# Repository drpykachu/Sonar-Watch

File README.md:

# Sonar Watch

### Hello all! 

### This project is inspired by something that I wanted to buy, but could not find online - so I decided to make it.

<div align="center">
  
</div>

### When the button is pressed, the watch sends out a "ping" to find the location of the hour (inner radial dot) and minute (outer radial dot), thus telling the time.

<div align="center">
  
  <br/>
  
  <br/>
  
  <br/>
  
</div>

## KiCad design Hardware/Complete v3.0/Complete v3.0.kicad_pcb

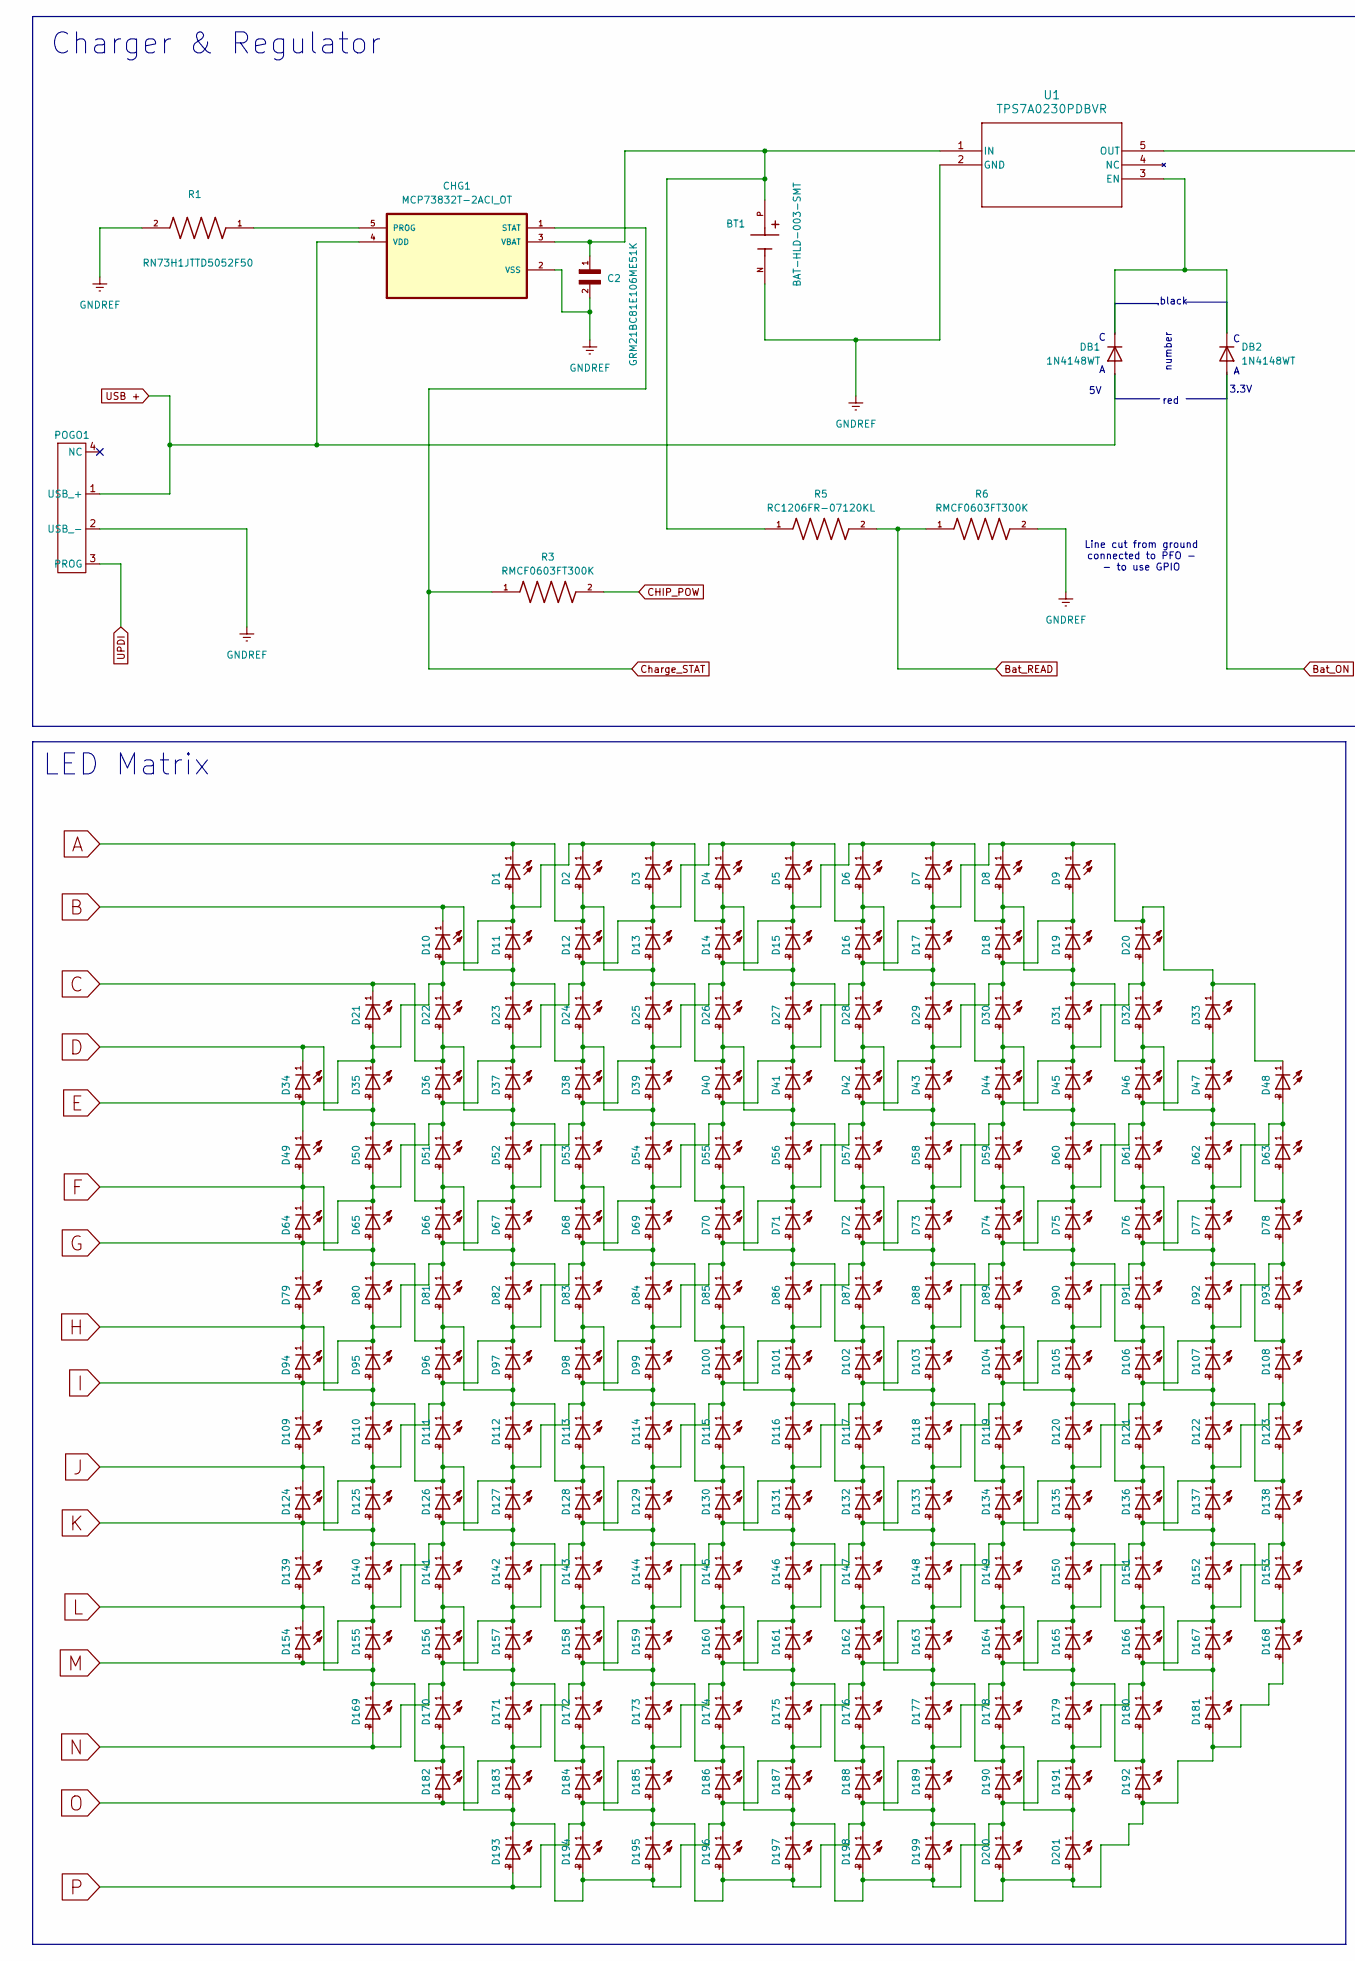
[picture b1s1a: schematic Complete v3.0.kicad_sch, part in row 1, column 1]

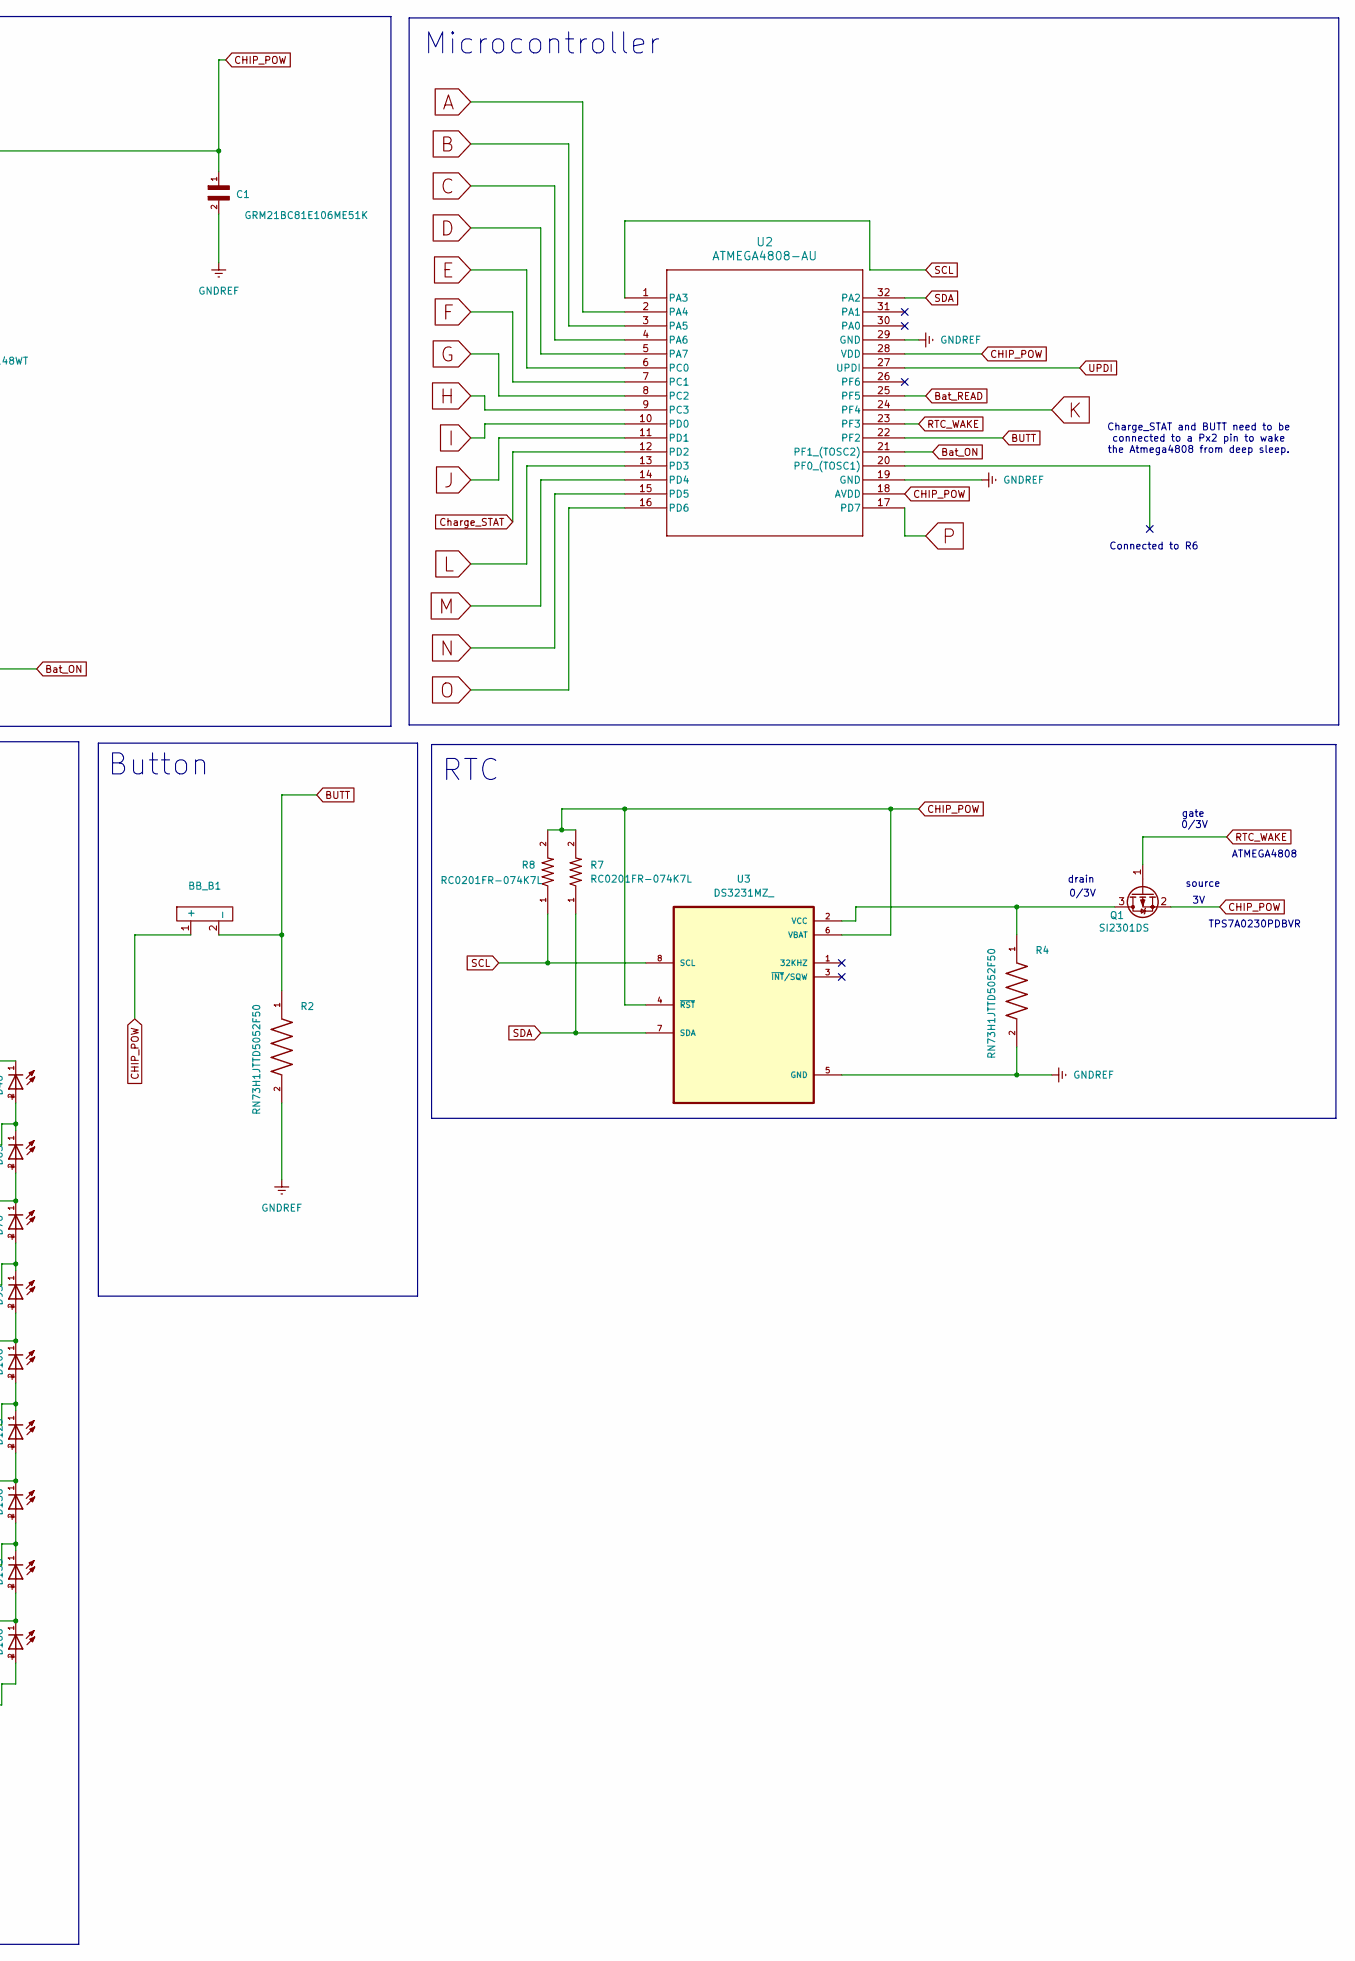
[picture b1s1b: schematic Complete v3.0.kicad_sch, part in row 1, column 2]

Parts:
BB_B1: BB_B
BT1: BAT-HLD-003-SMT; BAT_BAT-HLD-003-SMT_CUT; DigiKey_Part_Number 343-BAT-HLD-003-SMT-ND
C1, C2: GRM21BC81E106ME51K; CAPC2012X140N
CHG1: MCP73832T-2ACI_OT; SOT95P270X145-5N
D1, D2, D3, D4, D5, D6, D7, D8, D9, D10, D11, D12, D13, D14, D15, D16, D17, D18, D19, D20, D21, D22, D23, D24, D25, D26, D27, D28, D29, D30, D31, D32, D33, D34, D35, D36, D37, D38, D39, D40, D41, D42, D43, D44, D45, D46, D47, D48, D49, D50, D51, D52, D53, D54, D55, D56, D57, D58, D59, D60, D61, D62, D63, D64, D65, D66, D67, D68, D69, D70, D71, D72, D73, D74, D75, D76, D77, D78, D79, D80, D81, D82, D83, D84, D85, D86, D87, D88, D89, D90, D91, D92, D93, D94, D95, D96, D97, D98, D99, D100, D101, D102, D103, D104, D105, D106, D107, D108, D109, D110, D111, D112, D113, D114, D115, D116, D117, D118, D119, D120, D121, D122, D123, D124, D125, D126, D127, D128, D129, D130, D131, D132, D133, D134, D135, D136, D137, D138, D139, D140, D141, D142, D143, D144, D145, D146, D147, D148, D149, D150, D151, D152, D153, D154, D155, D156, D157, D158, D159, D160, D161, D162, D163, D164, D165, D166, D167, D168, D169, D170, D171, D172, D173, D174, D175, D176, D177, D178, D179, D180, D181, D182, D183, D184, D185, D186, D187, D188, D189, D190, D191, D192, D193, D194, D195, D196, D197, D198, D199, D200, D201: WL-SMCC_0402
DB1, DB2: 1N4148WT; D_SOD-523
POGO1: Untitled
Q1: SI2301DS; SOT-23
R1, R2, R4: RN73H1JTTD5052F50
R3, R6: RMCF0603FT300K
R5: RC1206FR-07120KL; RC1206FR_07120KL
R7, R8: RC0201FR-074K7L; RESC0603X26N
U1: TPS7A0230PDBVR
U2: ATMEGA4808-AU; TQFP-32_7x7mm_P0.8mm
U3: DS3231MZ_

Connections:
A: D1.1, D2.2, D12.1, D13.2, D25.1, D26.2, D40.1, D41.2, D56.1, D57.2, D72.1, D73.2, D88.1, D89.2, D104.1, D105.2, D120.1, D121.2, D136.1, D137.2, D152.1, D153.2, D168.1, U2.2 (PA4)
B: D10.1, D11.2, D23.1, D24.2, D38.1, D39.2, D54.1, D55.2, D70.1, D71.2, D86.1, D87.2, D102.1, D103.2, D118.1, D119.2, D134.1, D135.2, D150.1, D151.2, D166.1, D167.2, D181.1, U2.3 (PA5)
BUTT: BB_B1.2 (_), R2.1, U2.22 (PF2)
Bat_ON: DB2.2 (A), U2.21 (PF1_(TOSC2))
Bat_READ: R5.2, R6.1, U2.25 (PF5)
C: D21.1, D22.2, D36.1, D37.2, D52.1, D53.2, D68.1, D69.2, D84.1, D85.2, D100.1, D101.2, D116.1, D117.2, D132.1, D133.2, D148.1, D149.2, D164.1, D165.2, D179.1, D180.2, D192.1, U2.4 (PA6)
CHIP_POW: BB_B1.1 (+), C1.1, Q1.2 (S), R3.2, R7.2, R8.2, U1.5 (OUT), U2.18 (AVDD), U2.28 (VDD), U3.4 (~RST), U3.6 (VBAT)
Charge_STAT: CHG1.1 (STAT), R3.1, U2.12 (PD2)
D: D34.1, D35.2, D50.1, D51.2, D66.1, D67.2, D82.1, D83.2, D98.1, D99.2, D114.1, D115.2, D130.1, D131.2, D146.1, D147.2, D162.1, D163.2, D177.1, D178.2, D190.1, D191.2, D201.1, U2.5 (PA7)
E: D1.2, D2.1, D3.1, D4.2, D10.2, D11.1, D14.1, D15.2, D21.2, D22.1, D27.1, D28.2, D34.2, D35.1, D42.1, D43.2, D49.1, D58.1, D59.2, D74.1, D75.2, D90.1, D91.2, D106.1, D107.2, D122.1, D123.2, D138.1, U2.6 (PC0)
F: D49.2, D64.1, D65.2, D80.1, D81.2, D96.1, D97.2, D112.1, D113.2, D128.1, D129.2, D144.1, D145.2, D160.1, D161.2, D168.2, D175.1, D176.2, D181.2, D188.1, D189.2, D192.2, D199.1, D200.2, D201.2, U2.7 (PC1)
G: D3.2, D4.1, D5.1, D6.2, D12.2, D13.1, D16.1, D17.2, D23.2, D24.1, D29.1, D30.2, D36.2, D37.1, D44.1, D45.2, D50.2, D51.1, D60.1, D61.2, D64.2, D65.1, D76.1, D77.2, D79.1, D92.1, D93.2, D108.1, U2.8 (PC2)
GNDREF: BT1.N, C1.2, C2.2, CHG1.2 (VSS), POGO1.2 (USB_-), R1.2, R2.2, R4.2, R6.2, U1.2 (GND), U2.19 (GND), U2.29 (GND), U3.5 (GND)
H: D79.2, D94.1, D95.2, D110.1, D111.2, D126.1, D127.2, D138.2, D142.1, D143.2, D152.2, D153.1, D158.1, D159.2, D166.2, D167.1, D173.1, D174.2, D179.2, D180.1, D186.1, D187.2, D190.2, D191.1, D197.1, D198.2, D199.2, D200.1, U2.9 (PC3)
I: D5.2, D6.1, D7.1, D8.2, D14.2, D15.1, D18.1, D19.2, D25.2, D26.1, D31.1, D32.2, D38.2, D39.1, D46.1, D47.2, D52.2, D53.1, D62.1, D63.2, D66.2, D67.1, D78.1, D80.2, D81.1, D94.2, D95.1, D109.1, U2.10 (PD0)
J: D108.2, D109.2, D122.2, D123.1, D124.1, D125.2, D136.2, D137.1, D140.1, D141.2, D150.2, D151.1, D156.1, D157.2, D164.2, D165.1, D171.1, D172.2, D177.2, D178.1, D184.1, D185.2, D188.2, D189.1, D195.1, D196.2, D197.2, D198.1, U2.11 (PD1)
K: D7.2, D8.1, D9.1, D16.2, D17.1, D20.1, D27.2, D28.1, D33.1, D40.2, D41.1, D48.1, D54.2, D55.1, D68.2, D69.1, D82.2, D83.1, D96.2, D97.1, D110.2, D111.1, D124.2, D125.1, D139.1, U2.24 (PF4)
L: D78.2, D92.2, D93.1, D106.2, D107.1, D120.2, D121.1, D134.2, D135.1, D139.2, D148.2, D149.1, D154.1, D155.2, D162.2, D163.1, D169.1, D170.2, D175.2, D176.1, D182.1, D183.2, D186.2, D187.1, D193.1, D194.2, D195.2, D196.1, U2.13 (PD3)
M: D9.2, D18.2, D19.1, D29.2, D30.1, D42.2, D43.1, D56.2, D57.1, D70.2, D71.1, D84.2, D85.1, D98.2, D99.1, D112.2, D113.1, D126.2, D127.1, D140.2, D141.1, D154.2, D155.1, U2.14 (PD4)
N: D20.2, D31.2, D32.1, D44.2, D45.1, D58.2, D59.1, D72.2, D73.1, D86.2, D87.1, D100.2, D101.1, D114.2, D115.1, D128.2, D129.1, D142.2, D143.1, D156.2, D157.1, D169.2, D170.1, U2.15 (PD5)
unnamed: CHG1.5 (PROG), R1.1
unnamed: BT1.P, C2.1, CHG1.3 (VBAT), R5.1, U1.1 (IN)
unnamed: DB1.1 (K), DB2.1 (K), U1.3 (EN)
unnamed: Q1.3 (D), R4.1, U3.2 (VCC)
O: D33.2, D46.2, D47.1, D60.2, D61.1, D74.2, D75.1, D88.2, D89.1, D102.2, D103.1, D116.2, D117.1, D130.2, D131.1, D144.2, D145.1, D158.2, D159.1, D171.2, D172.1, D182.2, D183.1, U2.16 (PD6)
P: D48.2, D62.2, D63.1, D76.2, D77.1, D90.2, D91.1, D104.2, D105.1, D118.2, D119.1, D132.2, D133.1, D146.2, D147.1, D160.2, D161.1, D173.2, D174.1, D184.2, D185.1, D193.2, D194.1, U2.17 (PD7)
RTC_WAKE: Q1.1 (G), U2.23 (PF3)
SCL: R8.1, U2.1 (PA3), U3.8 (SCL)
SDA: R7.1, U2.32 (PA2), U3.7 (SDA)
UPDI: POGO1.3 (PROG), U2.27 (UPDI)
USB +: CHG1.4 (VDD), DB1.2 (A), POGO1.1 (USB_+)

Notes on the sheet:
Charge_STAT and BUTT need to be connected to a Px2 pin to wake the Atmega4808 from deep sleep.
TPS7A0230PDBVR
Microcontroller
Button
Charger & Regulator
0/3V
ATMEGA4808
Line cut from ground connected to PFO - - to use GPIO
number
3.3V
gate
Connected to R6
drain
black
RTC
LED Matrix
red
source

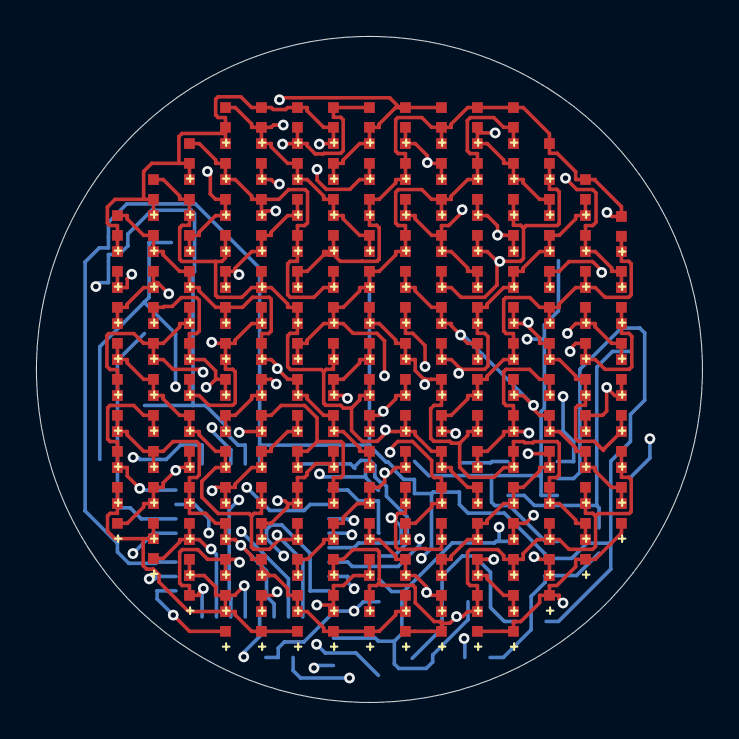
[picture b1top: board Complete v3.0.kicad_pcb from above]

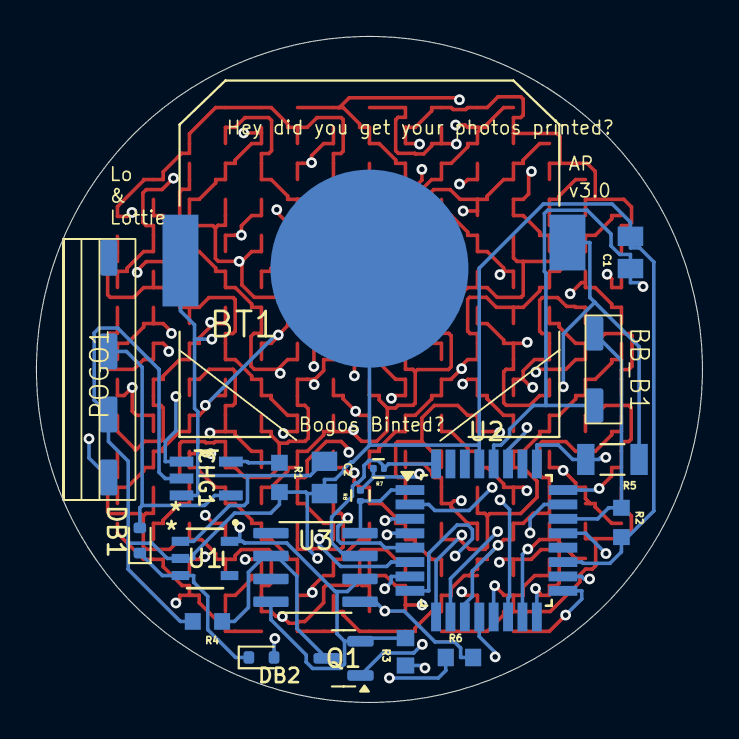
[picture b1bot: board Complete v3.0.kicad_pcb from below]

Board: 4 copper layers, 37.0 x 37.0 mm, 221 parts (20 on the bottom side), 31 nets.

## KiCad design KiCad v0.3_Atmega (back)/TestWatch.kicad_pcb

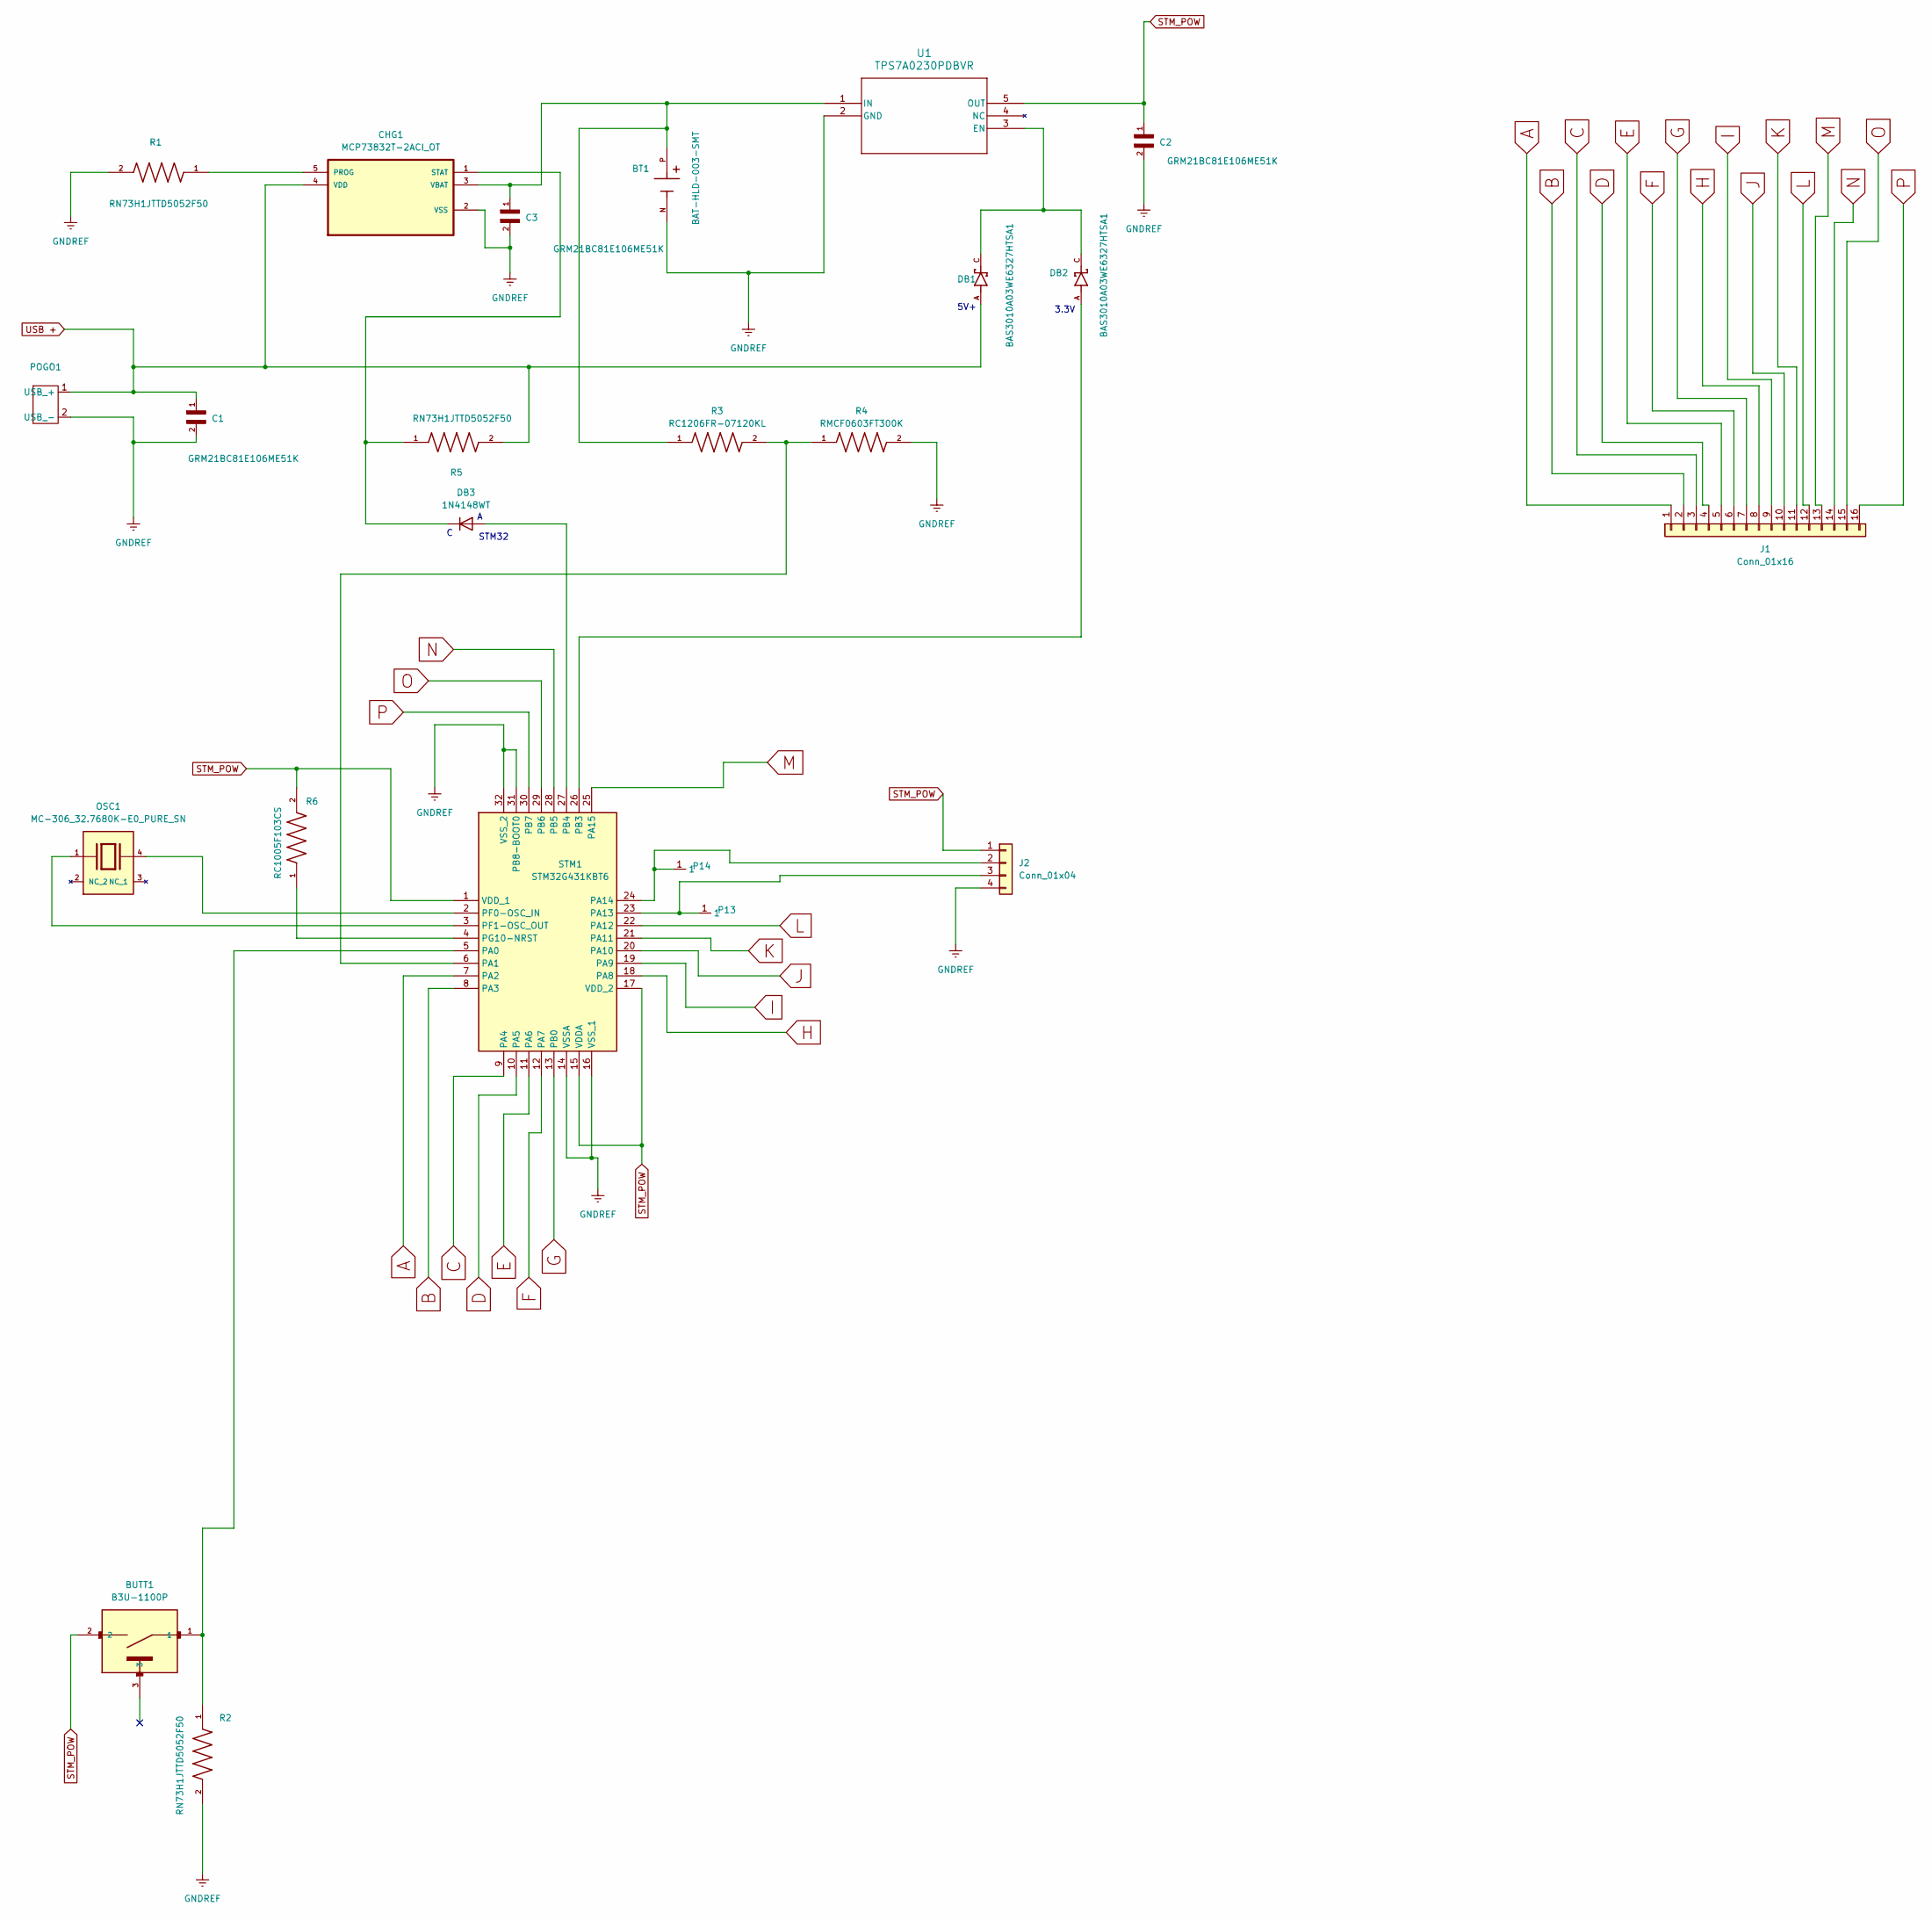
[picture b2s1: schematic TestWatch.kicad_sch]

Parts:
BT1: BAT-HLD-003-SMT; BAT_BAT-HLD-003-SMT_CUT; DigiKey_Part_Number 343-BAT-HLD-003-SMT-ND
BUTT1: B3U-1100P; SW_B3U-1100P
C1, C2, C3: GRM21BC81E106ME51K; CAPC2012X140N
CHG1: MCP73832T-2ACI_OT; SOT95P270X145-5N
DB1, DB2: BAS3010A03WE6327HTSA1; SOD2513X110N; PARTREV 2007-04-10
DB3: 1N4148WT; D_SOD-523
J1: Conn_01x16; PinHeader_1x16_P2.54mm_Vertical
J2: Conn_01x04; PinHeader_1x04_P2.54mm_Vertical
OSC1: MC-306_32.7680K-E0_PURE_SN; PARTREV N/A
P13, P14: PROGPAD
POGO1: Untitled
R1, R2, R5: RN73H1JTTD5052F50
R3: RC1206FR-07120KL; RC1206FR_07120KL
R4: RMCF0603FT300K
R6: RC1005F103CS; RESC1005X40N
STM1: STM32G431KBT6; QFP80P900X900X160-32N; Manufacturer_Part_Number STM32G431KBT6; Mouser Part Number 511-STM32G431KBT6
U1: TPS7A0230PDBVR

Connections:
A: J1.1, STM1.7 (PA2)
B: J1.2, STM1.8 (PA3)
C: J1.3, STM1.9 (PA4)
D: J1.4, STM1.10 (PA5)
E: J1.5, STM1.11 (PA6)
F: J1.6, STM1.12 (PA7)
G: J1.7, STM1.13 (PB0)
GNDREF: BT1.N, C1.2, C2.2, C3.2, CHG1.2 (VSS), J2.4, POGO1.2 (USB_-), R1.2, R2.2, R4.2, STM1.14 (VSSA), STM1.16 (VSS_1), STM1.31 (PB8-BOOT0), STM1.32 (VSS_2), U1.2 (GND)
H: J1.8, STM1.18 (PA8)
I: J1.9, STM1.19 (PA9)
J: J1.10, STM1.20 (PA10)
K: J1.11, STM1.21 (PA11)
L: J1.12, STM1.22 (PA12)
M: J1.13, STM1.25 (PA15)
N: J1.14, STM1.28 (PB5)
unnamed: CHG1.5 (PROG), R1.1
unnamed: CHG1.1 (STAT), DB3.1 (K), R5.1
unnamed: BT1.P, C3.1, CHG1.3 (VBAT), R3.1, U1.1 (IN)
unnamed: DB3.2 (A), STM1.27 (PB4)
unnamed: J2.2, P14.1, STM1.24 (PA14)
unnamed: J2.3, P13.1, STM1.23 (PA13)
unnamed: BUTT1.1, R2.1, STM1.5 (PA0)
unnamed: R3.2, R4.1, STM1.6 (PA1)
unnamed: DB2.A, STM1.26 (PB3)
unnamed: OSC1.4, STM1.2 (PF0-OSC_IN)
unnamed: OSC1.1, STM1.3 (PF1-OSC_OUT)
unnamed: R6.1, STM1.4 (PG10-NRST)
unnamed: DB1.C, DB2.C, U1.3 (EN)
O: J1.15, STM1.29 (PB6)
P: J1.16, STM1.30 (PB7)
STM_POW: BUTT1.2, C2.1, J2.1, R6.2, STM1.1 (VDD_1), STM1.15 (VDDA), STM1.17 (VDD_2), U1.5 (OUT)
USB +: C1.1, CHG1.4 (VDD), DB1.A, POGO1.1 (USB_+), R5.2

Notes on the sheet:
3.3V
STM32
5V+

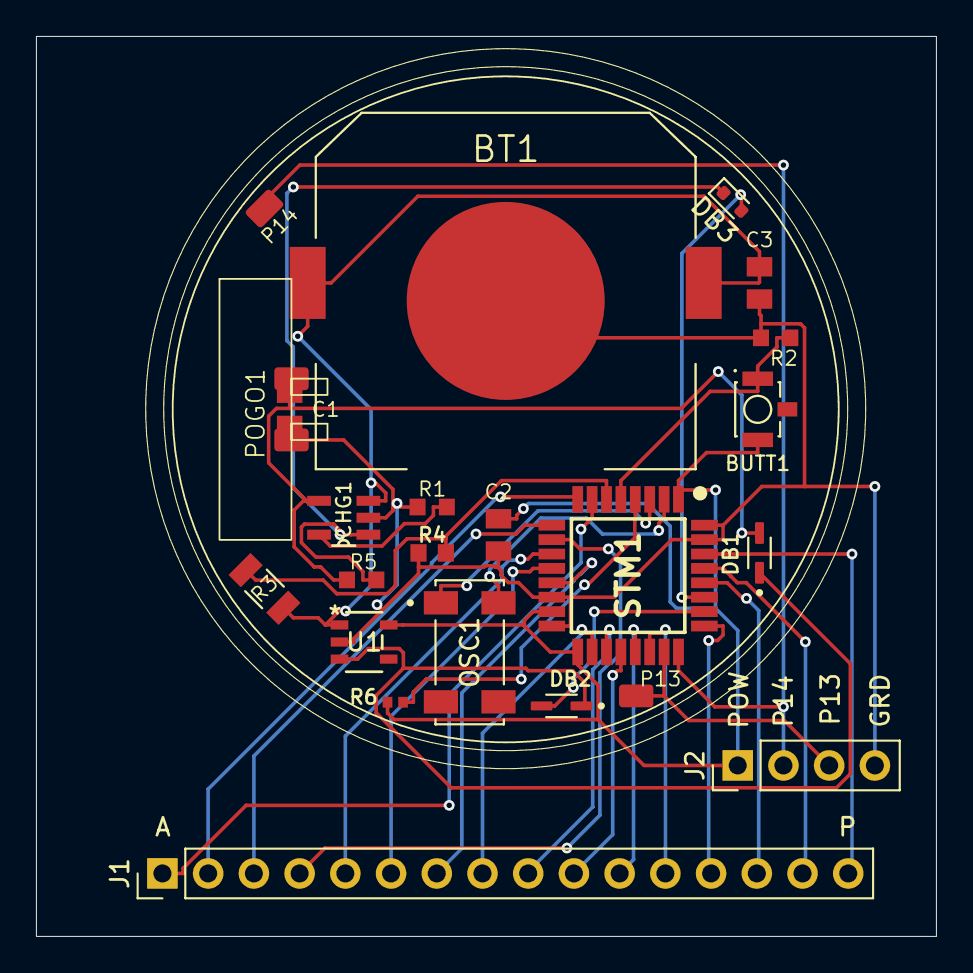
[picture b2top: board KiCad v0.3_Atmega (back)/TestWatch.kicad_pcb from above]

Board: 2 copper layers, 50.0 x 50.0 mm, 23 parts (0 on the bottom side), 32 nets.

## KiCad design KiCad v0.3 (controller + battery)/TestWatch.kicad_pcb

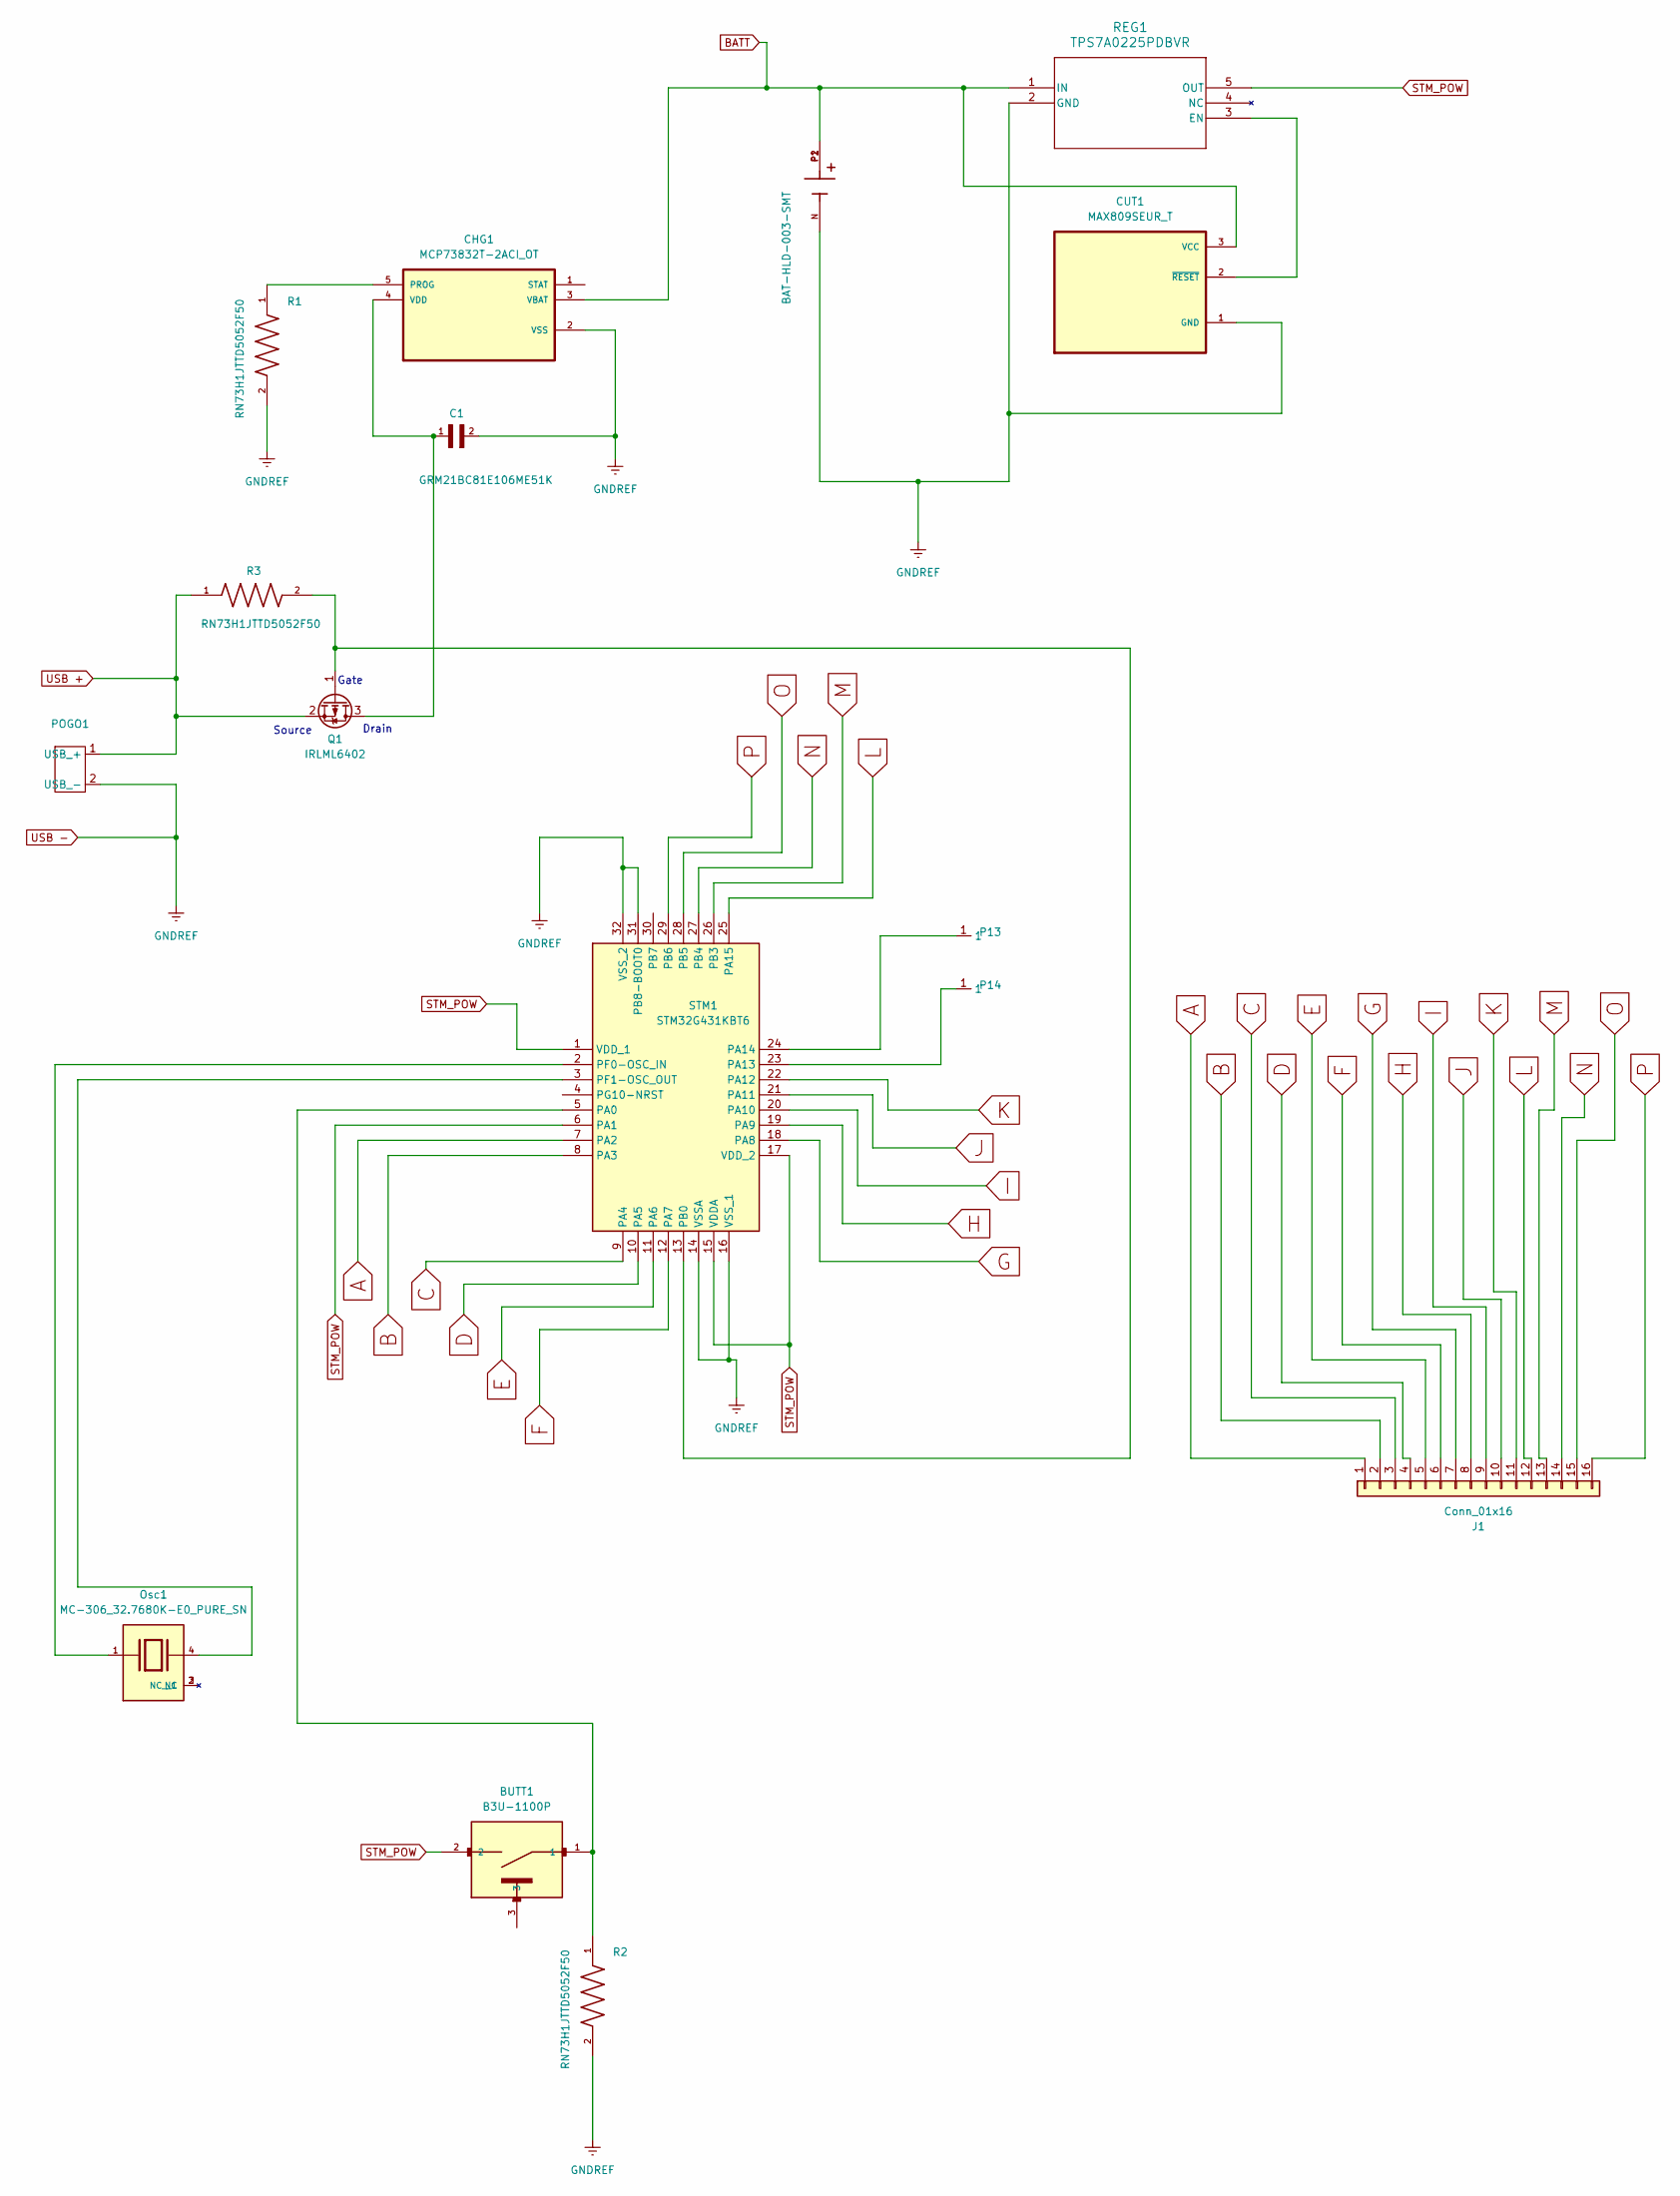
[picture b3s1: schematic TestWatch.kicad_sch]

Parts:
BT1: BAT-HLD-003-SMT; BAT_BAT-HLD-003-SMT_CUT; DigiKey_Part_Number 343-BAT-HLD-003-SMT-ND
BUTT1: B3U-1100P; SW_B3U-1100P
C1: GRM21BC81E106ME51K; CAPC2012X140N
CHG1: MCP73832T-2ACI_OT; SOT95P270X145-5N
CUT1: MAX809SEUR_T; MAX809SEUR+T
J1: Conn_01x16; PinSocket_1x16_P2.54mm_Vertical
Osc1: MC-306_32.7680K-E0_PURE_SN; PARTREV N/A
P13, P14: PROGPAD
POGO1: Untitled
Q1: IRLML6402; SOT-23
R1, R2, R3: RN73H1JTTD5052F50
REG1: TPS7A0225PDBVR
STM1: STM32G431KBT6; QFP80P900X900X160-32N; Manufacturer_Part_Number STM32G431KBT6; Mouser Part Number 511-STM32G431KBT6

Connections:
A: J1.1, STM1.7 (PA2)
B: J1.2, STM1.8 (PA3)
BATT: BT1.P1, BT1.P2, CHG1.3 (VBAT), CUT1.3 (VCC), REG1.1 (IN)
C: J1.3, STM1.9 (PA4)
D: J1.4, STM1.10 (PA5)
E: J1.5, STM1.11 (PA6)
F: J1.6, STM1.12 (PA7)
G: J1.7, STM1.18 (PA8)
H: J1.8, STM1.19 (PA9)
I: J1.9, STM1.20 (PA10)
J: J1.10, STM1.21 (PA11)
K: J1.11, STM1.22 (PA12)
L: J1.12, STM1.25 (PA15)
M: J1.13, STM1.26 (PB3)
N: J1.14, STM1.27 (PB4)
unnamed: CHG1.5 (PROG), R1.1
unnamed: C1.1, CHG1.4 (VDD), Q1.3 (D)
unnamed: CUT1.2 (~RESET), REG1.3 (EN)
unnamed: Q1.1 (G), R3.2, STM1.13 (PB0)
unnamed: BUTT1.1, R2.1, STM1.5 (PA0)
unnamed: P14.1, STM1.23 (PA13)
unnamed: P13.1, STM1.24 (PA14)
unnamed: Osc1.1, STM1.2 (PF0-OSC_IN)
unnamed: Osc1.4, STM1.3 (PF1-OSC_OUT)
O: J1.15, STM1.28 (PB5)
P: J1.16, STM1.29 (PB6)
STM_POW: BUTT1.2, REG1.5 (OUT), STM1.1 (VDD_1), STM1.6 (PA1), STM1.15 (VDDA), STM1.17 (VDD_2)
USB +: POGO1.1 (USB_+), Q1.2 (S), R3.1
USB -: BT1.N, C1.2, CHG1.2 (VSS), CUT1.1 (GND), POGO1.2 (USB_-), R1.2, R2.2, REG1.2 (GND), STM1.14 (VSSA), STM1.16 (VSS_1), STM1.31 (PB8-BOOT0), STM1.32 (VSS_2)

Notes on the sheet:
Source
Drain
Gate

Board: 2 copper layers, 16 parts (0 on the bottom side), 29 nets, no tracks yet.
